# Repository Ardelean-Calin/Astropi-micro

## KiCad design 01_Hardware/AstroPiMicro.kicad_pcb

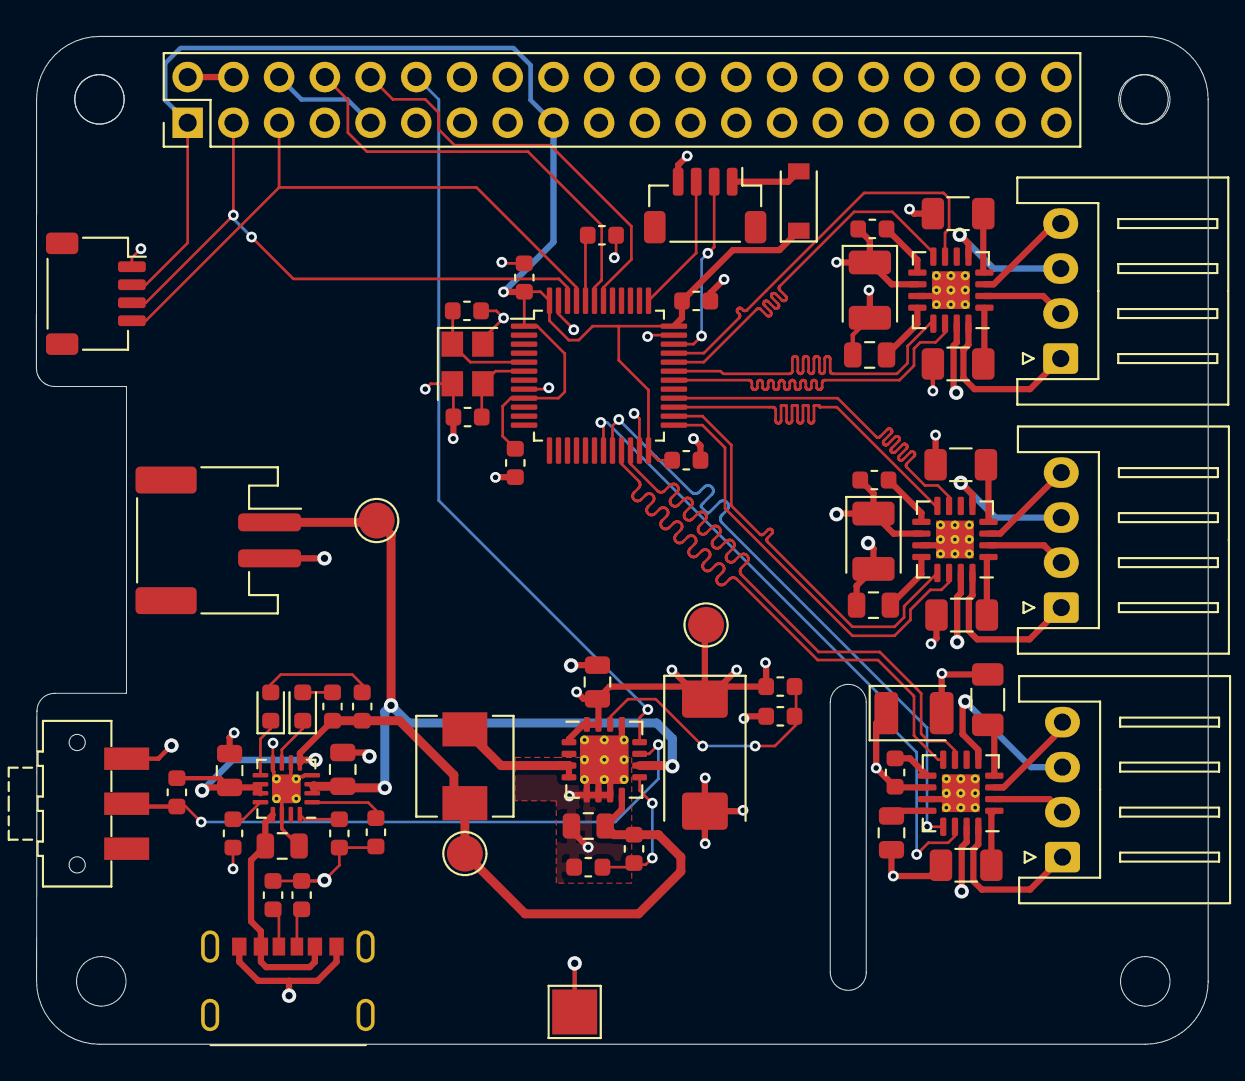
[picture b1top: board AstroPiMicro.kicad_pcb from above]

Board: 4 copper layers, 65.1 x 56.0 mm, 65 parts (0 on the bottom side), 66 nets.

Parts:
C1, C5: 20pF; C_0603_1608Metric
C2: 1uF; C_0805_2012Metric
C3: 4.7uF; C_0805_2012Metric
C4, C8: 10uF; C_0805_2012Metric
C6, C13, C17: 47uF; CP_EIA-3528-15_AVX-H
C7, C19, C20, C21: 100nF; C_0603_1608Metric
C9, C12, C15, C18: 2.2uF; C_0805_2012Metric
C10: 100uF; CP_EIA-7343-15_Kemet-W
C11, C14, C16: 10nF; C_0603_1608Metric
D1: Green; LED_0603_1608Metric
D2: Orange; LED_0603_1608Metric
D3: B5819W; D_SOD-123
J1: RPi Connector; PinHeader_2x20_P2.54mm_Vertical
J2: SHOU_HAN_TYPE-C_6P; SHOU HAN TYPE-C 6P
J3: 2-pin JST PH; JST_PH_S2B-PH-SM4-TB_1x02-1MP_P2.00mm_Horizontal
J4: 4-pin JST SH; JST_SH_SM04B-SRSS-TB_1x04-1MP_P1.00mm_Horizontal
J5: Stepper_Focus; JST_XH_S4B-XH-A_1x04_P2.50mm_Horizontal
J6: Stepper_Azimuth; JST_XH_S4B-XH-A_1x04_P2.50mm_Horizontal
J7: Stepper_Altitude; JST_XH_S4B-XH-A_1x04_P2.50mm_Horizontal
J8: SWD; JST_SH_BM04B-SRSS-TB_1x04-1MP_P1.00mm_Vertical
L1: 10uH; L_Sunlord_MWSA0518_5.4x5.2mm
QR*****: MiniCalinGeani
R1: 1.1k; R_0603_1608Metric
R2, R6, R21: 10k; R_0603_1608Metric
R3: 1.5k; R_0603_1608Metric
R4, R5: 5k1; R_0603_1608Metric
R7, R8: 1k; R_0603_1608Metric
R9, R12: 2M; R_0603_1608Metric
R10: 390k; R_0603_1608Metric
R11, R14: 1; R_1206_3216Metric
R13: 220k; R_0603_1608Metric
R16, R17, R19, R20: 220m; R_1206_3216Metric
SW1: SW_SPDT; SW_SPDT_CK-JS102011SAQN
TP1: TP_VBAT; TestPoint_Pad_D2.0mm
TP2: TP_Supply; TestPoint_Pad_D2.0mm
TP3: TP_5V; TestPoint_Pad_D2.0mm
TP4: TP_GND; TestPoint_Pad_2.5x2.5mm
U1: BQ24074RGT; VQFN-16-1EP_3x3mm_P0.5mm_EP1.6x1.6mm_ThermalVias
U2: STM32F103C8Tx; LQFP-48_7x7mm_P0.5mm
U3, U5, U6: DRV8833RTY; Texas_S-PWQFN-N16_EP2.1x2.1mm_ThermalVias
U4: TPS61030; Texas_S-PVQFN-N16_EP2.7x2.7mm_ThermalVias
Y1: 16MHz; Crystal_SMD_3225-4Pin_3.2x2.5mm

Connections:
+3V3: C7.1, C19.1, C20.1, C21.1, D3.1, J1.1, J1.17, J4.2, U2.1, U2.9, U2.24, U2.36, U2.48
+5V: C6.1, C9.1, C10.1, C11.1, C13.1, C14.1, C16.1, C17.1, J1.2, J1.4, R12.1, TP3.1, U3.10, U3.15, U4.1, U4.15, U4.16, U5.10, U5.15, U6.10, U6.15
+BATT: C3.1, J3.1, TP1.1, U1.2, U1.3, U4.10
/A1_ALT: U2.19, U5.14
/A1_AZ: U2.30, U6.14
/A1_FOCUS: U2.25, U3.14
/A2_ALT: U2.20, U5.13
/A2_AZ: U2.31, U6.13
/A2_FOCUS: U2.26, U3.13
/Alt_A1: J7.1, U5.16
/Alt_A2: J7.2, U5.2
/Alt_B1: J7.3, U5.5
/Alt_B2: J7.4, U5.3
/Az_A1: J6.1, U6.16
/Az_A2: J6.2, U6.2
/Az_B1: J6.3, U6.5
/Az_B2: J6.4, U6.3
/B1_ALT: U2.22, U5.7
/B1_AZ: U2.33, U6.7
/B1_FOCUS: U2.28, U3.7
/B2_ALT: U2.21, U5.8
/B2_AZ: U2.32, U6.8
/B2_FOCUS: U2.27, U3.8
/Focus_A1: J5.1, U3.16
/Focus_A2: J5.2, U3.2
/Focus_B1: J5.3, U3.5
/Focus_B2: J5.4, U3.3
/IMU_SCL: J1.5, J4.4, U2.45
/IMU_SDA: J1.3, J4.3, U2.46
/ON\~OFF: R21.2, SW1.2, U4.11
/SWCLK: J8.3, U2.37
/SWDIO: J8.2, U2.34
/UART_RX: J1.10, U2.42
/UART_TX: J1.8, U2.43
/Vsupply: C4.1, C8.1, L1.1, R7.1, R8.1, R9.1, R21.1, TP2.1, U1.5, U1.10, U1.11, U4.8
/~LOW_BAT: J1.12, U4.12
GND: C1.2, C2.2, C3.2, C4.2, C5.2, C6.2, C7.2, C8.2, C9.2, C10.2, C12.2, C13.2, C15.2, C17.2, C18.2, C19.2, C20.2, C21.2, J1.6, J1.9, J1.14, J1.20, J1.25, J1.30, J1.34, J1.39, J2.A12, J2.B12, J2.S1, J3.2, J4.1, J8.4, R1.1, R2.2, R3.1, R4.1, R5.1, R6.2, R10.2, R11.2, R13.2, R14.2, R16.2, R17.2, R19.2, R20.2, SW1.1, TP4.1, U1.4, U1.6, U1.8, U1.14, U1.17, U2.8, U2.23, U2.35, U2.47, U3.11, U3.17, U4.5, U4.6, U4.7, U4.13, U4.17, U5.11, U5.17, U6.11, U6.17, Y1.2, Y1.4
unnamed: C1.1, U2.5, Y1.1
unnamed: C5.1, U2.6, Y1.3
unnamed: C11.2, U3.9
unnamed: C12.1, U3.12
unnamed: C14.2, U5.9
unnamed: C15.1, U5.12
unnamed: C16.2, U6.9
unnamed: C18.1, U6.12
unnamed: D1.1, U1.7
unnamed: D1.2, R7.2
unnamed: D2.1, U1.9
unnamed: D2.2, R8.2
unnamed: D3.2, J8.1
unnamed: J2.A5, R4.2
unnamed: J2.B5, R5.2
unnamed: L1.2, U4.3, U4.4
unnamed: R1.2, U1.12
unnamed: R2.1, U2.44
unnamed: R3.2, U1.16
unnamed: R6.1, U1.1
unnamed: R9.2, R10.1, U4.9
unnamed: R11.1, U3.1
unnamed: R12.2, R13.1, U4.14
unnamed: R14.1, U3.4
unnamed: R16.1, U5.1
unnamed: R17.1, U5.4
unnamed: R19.1, U6.4
unnamed: R20.1, U6.1
VBUS: C2.1, J2.A9, J2.B9, U1.13

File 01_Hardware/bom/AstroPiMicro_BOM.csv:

Comment,Designator,Footprint,LCSC
"100uF","C10","CASE-D_7343","C122321"
"10nF","C11,C14,C16","0603","C57112"
"47uF","C6,C13,C17","CASE-B_3528","C147768"
"1uF","C2","0805","C28323"
"4.7uF","C3","0805","C1779"
"20pF","C1,C5","0603","C1648"
"100nF","C7,C19,C20,C21","0603","C14663"
"10uF","C4,C8","0805","C40894"
"2.2uF","C9,C12,C15,C18","0805","C49217"
"Green","D1","0603","C72043"
"Orange","D2","0603","C72038"
"B5819W","D3","SOD-123","C8598"
"RPi Connector","J1","Connector_PinHeader_2.54mm:PinHeader_2x20_P2.54mm_Vertical","C50982"
"SHOU_HAN_TYPE-C_6P","J2","SMD","C456012"
"2-pin JST PH","J3","Connector_JST:JST_PH_S2B-PH-SM4-TB_1x02-1MP_P2.00mm_Horizontal","C47647"
"4-pin JST SH","J4","Connector_JST:JST_SH_SM04B-SRSS-TB_1x04-1MP_P1.00mm_Horizontal","C145956"
"Stepper_Focus","J5","Connector_JST:JST_XH_S4B-XH-A_1x04_P2.50mm_Horizontal","C157925"
"Stepper_Azimuth","J6","Connector_JST:JST_XH_S4B-XH-A_1x04_P2.50mm_Horizontal","C157925"
"Stepper_Altitude","J7","Connector_JST:JST_XH_S4B-XH-A_1x04_P2.50mm_Horizontal","C157925"
"SWD","J8","Connector_JST:JST_SH_BM04B-SRSS-TB_1x04-1MP_P1.00mm_Vertical","C145956"
"10uH","L1","SMD-PIND-5.2x5.4x2.8_1.2x2.2","C139506"
"1.1k","R1","0603","C22764"
"390k","R10","0603","C23150"
"1","R11,R14","1206","C17928"
"220k","R13","0603","C22961"
"220m","R16,R17,R19,R20","1206","C25336"
"1.5k","R3","0603","C22843"
"5k1","R4,R5","0603","C23186"
"10k","R2,R6,R21","0603","C25804"
"1k","R7,R8","0603","C21190"
"2M","R9,R12","0603","C22976"
"SW_SPDT","SW1","Button_Switch_SMD:SW_SPDT_CK-JS102011SAQN","C221660"
"BQ24074RGT","U1","QFN-16_EP_3.0x3.0x0.5P","C54313"
"STM32F103C8Tx","U2","LQFP-48_7.0x7.0x0.5P","C8734"
"DRV8833RTY","U3,U5,U6","QFN-16_EP_4.0x4.0x0.65P","C154936"
"TPS61030","U4","QFN-16_EP_4.0x4.0x0.65P","C10110"
"16MHz","Y1","SMD-3225_4P","C13738"

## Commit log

2020-05-11 Added gitignore
2020-05-11 First hardware version
2020-05-11 Added some documentation
2020-05-11 Renamed Documentation folder
2020-05-11 Generated code skeleton
2020-05-11 Finished board outline
2020-05-14 Routing finished.
2020-05-15 Added bom
2020-05-15 Removed unused files
2020-05-15 Almost all footprints have MFN now
2020-05-17 Finished BOM, PCB and ordered PCB
2020-07-08 Hardware v1.0
2020-07-17 Started on HW version 2
2020-07-20 Ordered PCBs from JLCPCB
2020-07-27 Changed layers to Sig, GND, PWR, Sig
